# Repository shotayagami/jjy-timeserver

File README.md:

# JJY タイムサーバ (Raspberry Pi 4)

```
ntp.nict.jp ──NTP──▶ chrony ──システム時刻──▶ jjyd ──GPIO(ケーブル)──▶ JJY 送信ユニット ──40/60kHz(基板上のコイル)──▶ 電波時計
                       └──NTP──▶ 宅内LANのPC等
```

| ディレクトリ | 内容 |
|---|---|
| [hardware/](hardware/README.md) | 送信ユニット基板の回路・部品表・コイル・調整手順 |
| [hardware/kicad/](hardware/kicad) | KiCad 回路図・基板データ(100×96mm、J1 は上辺中央、基板上コイル、LCD、RTC) |
| [server/jjyd/](server/jjyd) | JJY エンコーダと送信デーモン(Python) |
| [server/config/](server/config) | chrony(NICT同期+LAN向けNTP) と jjyd の設定 |
| [server/systemd/](server/systemd) | systemd ユニット |
| [scripts/install.sh](scripts/install.sh) | Raspberry Pi OS 向けインストーラ |

## 仕組み

- **時刻取得**: chrony が `ntp.nict.jp` に 64 秒以上の間隔で問い合わせ、システム時刻を数 ms 以内に保つ。
- **フレーム生成**: [encoder.py](server/jjyd/encoder.py) が JST で 60 秒分のコード(分・時・通算日・年・曜日・パリティ)を作る。うるう秒は tzdata の leap-seconds.list から予定を読み、LS1/LS2 の予告(前月2日 9:00 JST 〜)と、実施月1日 8:59 JST の 61 秒(挿入)/59 秒(削除)フレームに対応する([leap.py](server/jjyd/leap.py)、`[leap]`)。挿入の 60 秒目は、カーネルが時計を1秒戻している間なので単調時計で送る。毎時 15 分・45 分も既定では通常フレームを送る。NICT 準拠の呼出符号フレーム(40〜49 秒に "JJY" のモールス、50〜55 秒を停波予告 ST に置き換え、年・曜日・うるう秒情報は送らない)は `[callsign] enabled = true` のときだけ送る(下の「法令・商標」参照)。
- **送信**: PWM0(GPIO18)が常時 40/60kHz を出し、GPIO23 が毎秒の頭で最大振幅にしてマーカー 0.2 s / "1" 0.5 s / "0" 0.8 s 後に 10% へ戻す。
- **表示**: 基板の LCD(16×2、I2C)に毎秒、日付・曜日・時刻・送信周波数・送信状態を表示する(`[lcd]`)。
- **送信信号 LED**: 低レベル期間だけ点灯する(ビット1=0.5秒、ビット0=0.2秒点灯して消灯、マーカー=0.8秒。`[signal]`)。
- **画面のモニタ**(`jjymon`): Pi の HDMI 画面に、JST の時計、jjyd が今送っているパルス(直近 10 秒の搬送波の波形)、1 分 60 秒のフレーム全体(今の秒を強調)、基板の LED D1(赤・高レベル)・D2(黄緑・低レベル)・D3(黄・通電)の点灯の再現、chrony の同期状態と時刻源の一覧、サービスの状態・CPU 温度を出す。jjyd が秒ごとに `/run/jjyd/status.json`(`[status]`)へ書く状態を読み、送信のタイミングには影響しない。インストーラが `/usr/local/bin/jjymon` と `/etc/xdg/autostart/jjymon.desktop`(デスクトップへのログイン時に全画面で自動起動。Esc で終了、F11 で全画面の切替)を入れる。不要なら `JJY_MONITOR=0` でインストールする。手で試すときは `jjymon --windowed`。LED は、フレームと時刻から jjyd の規則(`send_pulse`)どおりに計算した再現で、基板の GPIO を読んだものではない(基板が無くても動く)。
- **RTC が無い構成**(`JJY_RTC=0`): インストーラが `fake-hwclock` を入れ、時刻を 1 時間ごとと停止時に保存する(`systemd-timesyncd` を止めると、起動時の時計が古い保存時刻のままになるため)。起動直後のずれが縮まり、chrony が同期するまでの時計が実際に近くなる。jjyd は同期するまで送信しない。
- **RTC**: 基板上の DS3231 + CR2032 を使い、再起動直後でも前回同期から 24 時間以内なら送信を続ける(`[rtc]`、既定で有効)。
- **安全動作**: `chronyc tracking` が非同期なら送信停止。`local stratum 10` の自己参照(起動直後)や、同期先を選んだ後でもステップ補正が済むまで時計がずれている間(システム時刻のずれ 0.25 秒超)も、同期済みとみなさない(実機で起動直後に約 160 秒ずれていたため)。同期喪失後も `holdover_s`(既定6時間)までは送信継続。起動後に一度も同期していなければ送信しない。

## セットアップ

1. [hardware/README.md](hardware/README.md) に従い基板を製作し、Pi の GPIO ヘッダに**ケーブルでつなぐ**(40 ピンのフラットケーブル、またはジャンパ線)。基板は Pi のケースの外に置く。
2. Pi にこのリポジトリを置き `sudo ./scripts/install.sh` → `sudo reboot`
3. 確認
   - `chronyc sources -v` / `chronyc tracking` で NICT に同期していること
   - `sudo systemctl start jjyd && journalctl -u jjyd -f`
   - `python3 -m jjyd --dry-run` でハード無しでもタイミングログを確認可能
4. 既定は西日本 60kHz(はがね山)。東日本にする場合は `/etc/jjyd.toml` の `khz = 40` にして jjyd を再起動する(基板にスイッチは無く、周波数はソフトだけで切り替わる)。

## 開発・テスト

```
cd server
python -I tests/test_encoder.py        # エンコーダのラウンドトリップ/構造テスト
python -I tests/test_timesync.py       # 同期監視と RTC の判定
python -I tests/test_lcd_signal.py     # LCD 表示と信号 LED のタイミング
python -I tests/test_monitor.py        # モニタ(信号の再現、状態ファイル、chronyc の解析)
python -m jjyd --print-frame           # 現在の分のフレームを表示
# 画面の試験: 呼出符号のフレームを 20 分ごと(毎時 0・20・40 分)に出す。GPIO は使わず、状態は別のファイルへ書くので、動いている jjyd や jjymon には影響しない
python -m jjyd --dry-run --test-callsign-every 20 --status /tmp/jjy-test.json &
python -m jjymon --status /tmp/jjy-test.json --windowed
```

## 法令・商標

- **免許**: 免許が要らないのは、電波が[著しく微弱な無線局](https://laws.e-gov.go.jp/law/325M50080000014)(電波法第4条第1号、施行規則第6条: 322MHz以下では 3m で 500µV/m 以下)の範囲に収まる場合だけです。超えると無免許開設(電波法第110条)です。基板の出力は計算値で約 40µV/m(hardware/README.md)ですが、**実機での測定(告示の方法)は未実施**です。測定せずに出力を上げたり、外付けアンテナをつないだりしないでください。
- **呼出符号**: 「JJY」は NICT の局の呼出符号であり、NICT の登録商標(T4355749)でもあります。既定では送らず(`[callsign] enabled = false`)、15・45 分も通常のフレームを送ります。電波時計の受信にはこれで十分です。有効にするのは、用途と責任を理解したうえで自分で判断する場合だけにしてください。基板・ソフトを頒布・販売する場合は商標の扱いにも注意してください。
- **利用範囲**: 自分の時計を合わせる目的に限り、他人の機器に影響しない範囲(時計のすぐそば)で使ってください。ここに書いたことは法的助言ではありません。最終的な適法性の確認は利用者の責任です。

## 注意

- 電波は**微弱無線局の範囲(322MHz以下: 3mで500µV/m以下)**に収め、時計のすぐそばでのみ受かる出力にすること。
- 精度は Linux のユーザ空間タイミング(数百 µs〜数 ms)で、電波時計の許容(数十 ms)には十分。未確認の点は実機での電界強度と受信確認。
- 未実機検証: ハードウェア回路・sysfs PWM・systemd 部分は Pi 上でまだ試していない。エンコーダのみ PC でテスト済み。

## ライセンス

- ソフトウェア(`server/`、`scripts/`): [MIT License](LICENSE)
- ハードウェア(`hardware/` の回路図・基板・ガーバー・BOM): [CERN-OHL-P-2.0](hardware/LICENSE)(許容型)
- 基板データには KiCad 標準ライブラリのフットプリント/シンボルが含まれる。KiCad ライブラリのライセンス(CC-BY-SA 4.0 とデザインへの使用に関する例外)に従う。

## 現状と注意

- 設計段階のデータです。**基板は未発注・未製造で、Raspberry Pi 実機でも未検証**です(エンコーダとタイムシンクの単体テストと、KiCad の ERC/DRC のみ確認済み)。
- 電波は微弱無線局の範囲に収めること。各国・地域の電波法に従う責任は利用者にあります。
- 部品の在庫・品番は変動します。発注前に必ず再確認してください([hardware/kicad/fab/README.md](hardware/kicad/fab/README.md))。

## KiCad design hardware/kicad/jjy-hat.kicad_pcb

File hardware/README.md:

# JJY 送信ユニット(Raspberry Pi 4 用・40kHz / 60kHz ソフト切替)

Raspberry Pi の GPIO に**ケーブルでつなぐ**別基板です(Rev C)。次をすべて 1 枚に載せています。

- JJY 仕様の振幅変調(最大 100% / 低レベル 10%)をした 60kHz(はがね山・既定)/ 40kHz(おおたかどや山)の送信回路
- **アンテナ**: 基板上のスパイラルコイル(部品なし)と、外付けアンテナ用の端子(J2)の **2 択**(ジャンパ JP1 で選ぶ)
- 現在時刻を表示する LCD(16×2、I2C)と、送信信号を示す LED
- RTC(DS3231 + CR2032)

金属ケース(GPIO が細いスリットから見えるタイプ)の中の Pi にも使えるよう、Pi に挿す HAT ではなく、**ケースの外に置く基板**にしてあります(100×96mm)。
**J1 は基板の上辺の中央**にあり、ケーブルは上へ出ます。その下に送信回路と RTC、右下にコイル、左下に LCD の取り付け位置(J3)があります。

## Pi との接続(J1)

J1 は **2×20 の 2.54mm ピンヘッダ**(Pi の GPIO ヘッダと同じ並び・同じピン番号)です。2 通りの接続ができます。

- **40 ピンのフラットケーブル(1 対 1)**: Pi 側にメスのソケット、基板側に 2×20 の IDC ソケット。ピン 1 の印(赤線)を合わせる。
- **ジャンパ線(Dupont)**: 必要なピンだけを 1 本ずつつなぐ。

使うピン(Pi の物理ピン番号):

| 用途 | Pi のピン | 信号 |
|---|---|---|
| 電源 | 1 または 17 | 3V3 |
| GND | 6 / 9 / 14 など(どれか 1 本以上) | GND |
| I2C(LCD・RTC) | 3 / 5 | SDA(GPIO2)/ SCL(GPIO3) |
| キャリア | 12 | GPIO18(PWM0) |
| 振幅切替 | 16 | GPIO23 |
| 送信信号 LED | 18 | GPIO24 |

- **ケースへの配線**: ケースの蓋にピンの名前が印刷されているので、見ながらつなげる。スリットの寸法・深さは**実物で確認**すること(ソケットが入らない場合は、ジャンパ線を使う)。
- 基板側の J1 は、使う信号だけジャンパ線でつなげば、40 ピンすべてを配線する必要はない。

## 回路

```
 GPIO18 ──┬──────── U1A in (2), U1B in (5)  (R4 10k で GND へプルダウン)
 GPIO23 ──┴─── U1B /OE (4) ─── R3 10k で 3V3 へプルアップ、D1 のカソードへ
                                   3V3 ── R5 1k ── D1(赤 LED)
 U1A(/OE=GND, 常時有効)出力 ── R1 10k ──┐
                                           ├── 駆動ノード ── JP1 ─┬─(2-3)─ L1(基板コイル)── GND
                                           │                      └─(1-2)─ J2(外付けアンテナ)── GND
 U1B(GPIO23=Low で有効)出力 ── R2 1.1k ──┘

 GPIO24 ── R7 330 ── D2(緑 LED)── GND      送信信号 LED
 3V3 ── R8 470 ── D3(黄 LED)── GND          通電表示(パイロットランプ。常時点灯)
 U1: VCC(14)=3V3 (C1 100nF)、GND(7)。未使用ゲート(C, D)の入力は GND。
```

- **U1A** は常にキャリアを出す(R1 経由 = 低レベル)。**U1B** は GPIO23 が Low の間だけ加わる(R2 が並列 = 高レベル)。
- 高レベルと低レベルの電流比は、駆動抵抗がコイルより十分大きいので **1 + R1/R2**(= 約 10.1 倍、-20dB、約 10%)。
- D1(赤)は高レベル(最大振幅)の間だけ点灯する(0.2 / 0.5 / 0.8 秒)。

## 部品表

| 記号 | 部品 | 備考 |
|---|---|---|
| U1 | 74LVC125A(SOIC-14、LCSC C7661) | JLCPCB で実装 |
| U2 | DS3231SN#(SOIC-16W、LCSC C722469) | JLCPCB で実装(RTC) |
| K1 | AQY212SX(フォトモスリレー、SOP-4、LCSC C719754) | JLCPCB で実装(共振オプション用。通常は使わない) |
| J1 | 2×20 ピンヘッダ(2.54mm、ストレート) | 手はんだ |
| R1 | 10kΩ 1/4W 金属皮膜 1%(リード) | 常時キャリア。R2 の約 9 倍にする |
| R2 | 1.1kΩ 1/4W 金属皮膜 1%(リード) | 高レベルのとき並列 |
| R3, R4 | 10kΩ 1/4W(リード) | プルアップ/プルダウン |
| R5 | 1kΩ 1/4W(リード) | D1 の電流制限 |
| R7 | 330Ω 1/4W(リード) | D2 の電流制限 |
| R8 | 470Ω 1/4W(リード) | D3 の電流制限(約 2.8mA) |
| D1 | 3mm 赤 LED(リード、Vf 約 2V) | 高レベル表示。四角いパッドがカソード |
| D2 | 3mm 緑 LED(リード、Vf 約 2V) | 送信信号 LED。四角いパッドがカソード |
| D3 | 3mm 黄 LED(リード、Vf 約 2V) | 通電表示(パイロットランプ)。四角いパッドがカソード |
| C1, C6 | 100nF 50V 積層セラミック(リード、足の間隔 5.08mm) | U1 / U2 のバイパス |
| BT1 | CR2032 ホルダ MYOUNG BS-07-A1BJ001(LCSC C2979167) + CR2032 | RTC のバックアップ。手はんだ |
| J3 | 1×4 ピンソケット(2.54mm) | LCD 用(下記) |
| L1 | 基板上のスパイラルコイル | 部品は不要(基板の配線) |
| JP1 | 1×3 ピンヘッダ(2.54mm)+ 短絡ピン(ジャンパ)1 個 | アンテナ選択。1-2 短絡 = 外付け(J2)/ 2-3 短絡 = 基板コイル |
| J2 | 1×2 ピンヘッダ(2.54mm) | 外付けアンテナ(コイル)の接続。向きは問わない |

リード部品は**手はんだ**です(JLCPCB では実装しません)。抵抗は縦置き(足の間隔 2.54mm)、コンデンサは基板の穴が 5.00mm なので足を少し曲げて入れます。

## アンテナの選択(JP1)と外付けアンテナ(J2)

駆動信号は JP1 の中央のピン(2)に来ています。**短絡ピン(ジャンパ)をどちらに挿すかで、アンテナを選びます**(選ばれなかった側は開放になり、電波は出ません)。

| JP1 の短絡 | 使うアンテナ |
|---|---|
| 1-2 | 外付けアンテナ(J2 に接続) |
| 2-3 | 基板コイル(L1)← 標準 |
| なし | どちらにも出力しない |

### 外付けアンテナを使うとき(重要: R1/R2 を交換する)
- 外付けのフェライトバーなどは、基板のコイルよりずっと強い磁界が出ます(巻数 × 断面積 × 棒の透磁率が大きいため)。**基板コイル用の R1/R2(10kΩ / 1.1kΩ、電流 約 2mA)のままつなぐと、微弱無線局の限度を超えるおそれがあります。**
- そこで、外付けアンテナに替えるときは、**R1 と R2 をもっと大きな値に交換**して電流を減らします(リード部品なので交換は容易)。比は R1 = 約 9 × R2 を保ちます。
- 目安(フェライトバー: 直径 10mm × 長さ 100mm、100 回巻きの場合。**概算なので必ず実測で確認**):

| R1 / R2 | 電流(基本波のピーク) | 備考 |
|---|---|---|
| 220kΩ / 24kΩ | 約 0.1mA | 最初はこの値から。受からなければ下げる |
| 100kΩ / 11kΩ | 約 0.2mA | |
| 68kΩ / 7.5kΩ | 約 0.3mA | 概算で限度に近づく。実測が必須 |

- 巻数が少ない小さなコイルなら、基板コイル用の値(10kΩ / 1.1kΩ)のままでも使えます。目安は「巻数 × 面積 × 電流」が基板コイル(30 回 × 約 3cm² × 2mA)と同程度までです。
- 基板コイルに戻すときは、R1/R2 を 10kΩ / 1.1kΩ に戻し、JP1 を 2-3 にします。
- J2 のコイルには直流が流れません(駆動は交流のみ)。インダクタンスは 0.1〜3mH 程度で、厳密でなくて構いません(共振させていないため)。

## 共振オプション(外付けアンテナ用・通常は未実装)

外付けアンテナ(J2)側には、以前の設計と同じ**直列共振回路と、40kHz / 60kHz をソフトで切り替えるフォトモスリレー K1**の部品を置く場所を用意してあります(K1 だけは JLCPCB で実装済み、他の部品は**載せない**のが標準)。基板コイル(L1)側には影響しません。

構成(JP1 を 1-2 にしたとき): `JP1.1 → [共振コンデンサ] → J2.1(外付けアンテナ)→ GND`

| 記号 | 部品 | 役割 |
|---|---|---|
| JP2 | 1×2 ピンヘッダ + 短絡ピン | 短絡 = 共振回路をバイパス(標準)/ 短絡なし = 共振コンデンサを通す |
| C2・C3・C4 | 4.7nF・2.2nF・150pF(C0G、50V、±5%) | 60kHz 用(合計 7.05nF、1mH のコイルで約 59.9kHz) |
| C5 | 数 pF〜数十 pF | 60kHz の微調整用 |
| C7・C8・C9 | 4.7nF・2.2nF・2.2nF(C0G、50V、±5%) | 40kHz 用に K1 経由で追加(合計 16.15nF で約 39.6kHz) |
| K1 | AQY212SX(フォトモスリレー、SOP-4、LCSC C719754) | 実装済み。GPIO21(J1 の 40 番ピン)で 40kHz 用の C7〜C9 を接続 |
| R6 | 330Ω 1/4W | K1 の LED の電流制限 |

### 実装する手順
1. JP2 の短絡ピンを外す。
2. C2・C3・C4(と必要なら C5)を実装する。1mH 前後の外付けコイルなら、60kHz で共振する。
3. 40kHz も使うなら、R6・C7〜C9 も手はんだする(K1 は実装済み)。
4. `/etc/jjyd.toml` の `select_gpio = 21` の行を有効にして、`sudo systemctl restart jjyd`。40kHz のときだけ GPIO21 が High になり、K1 が C7〜C9 を追加する。
5. 同調は使うコイルの L で変わるので、**各周波数でアンテナ電流を測って調整**する(C = 1 / ((2πf)² · L))。

### 注意(重要)
- 共振させると電流が増えます。共振の効果は、駆動抵抗(R1/R2 の並列)がコイルのリアクタンス(1mH・60kHz で約 380Ω)と同程度以下のときに出ます。標準の R1/R2(10kΩ / 1.1kΩ)では、共振させても電流はほとんど変わりません。
- 共振で電流を増やすために R1/R2 を小さくすると、**微弱無線局の限度を超えやすくなります**。外付けコイルの巻数を減らす、電流を測る、など実測で確認してください。
- K1 は SMD 部品で、JLCPCB が実装します(R6 と C7〜C9 が無いうちは何も接続されず、動作に影響しません)。ピン配置(1=LED+、2=LED−、3/4=負荷)と LED 電流はデータシートで未確認です。
- 未確認: この共振オプションは、実機で試していません。

## アンテナ(基板上のスパイラルコイル L1)

基板の右下に、外形 26mm 角の**四角いスパイラルコイル**を両面に作っています(表面は外側から内側へ、中心の穴で裏面へ移り、裏面は内側から外側へ)。

| 項目 | 値(生成スクリプトの計算 / 概算) |
|---|---|
| 巻数 | 約 15 回/面、合計約 30 回 |
| 配線長 | 約 2m(幅 0.25mm、ピッチ 0.6mm) |
| 直流抵抗 | 約 4Ω |
| インダクタンス | 約 15µH(概算。実測すること) |

- **共振はさせません**。駆動抵抗(約 1kΩ)がコイルのリアクタンス(60kHz で約 6Ω)よりはるかに大きいので、電流は抵抗だけで決まります。そのため、従来の共振コンデンサと帯域切替のスイッチ(K1)は**廃止**しました。40kHz / 60kHz の切替は**ソフトの `khz` の設定だけ**です。
- **銅ベタ禁止**: コイルの範囲は、表裏とも GND の銅ベタを抜いてあります(コイルの下に銅があると、渦電流で磁界が弱くなります)。
- **金属を近づけない**: コイルの近く(特に上や下)に金属板を置かないでください。
- 高レベルのアンテナ電流は約 2mA(2.1V ÷ R1・R2 の並列 約 1kΩ)。コイルが小さい分、電流を大きくして磁界の強さを保っている。

### 電界強度の概算(重要・実測で必ず確認)
上のコイルを、巻数 30、平均面積 2.9×10⁻⁴ m²、電流 2mA の磁気双極子として概算した値です。**概算は数十 dB の誤差があり得ます。**

| 距離 | 電界強度の目安 | 備考 |
|---|---|---|
| 3m | 約 40µV/m | 微弱無線局の限度(3m で 500µV/m)に対して約 20dB の余裕 |
| 1m | 約 1mV/m | |
| 0.3m | 約 40mV/m | 時計に近づける距離 |

- 時計は、基板のコイルの上や横に、**数 cm〜30cm** まで近づけて使います。
- 受信できないときは、(1) 近づける、(2) R1/R2 を同じ倍率で下げて電流を増やす(比 R1 = 約 9 × R2 を保つ)、の順に試します。
- **出力を上げた場合は、微弱無線局の範囲を超えていないか、必ず測定で確認してください。**

### R1 と R2 を変えるときのルール
- 高低の比(約 10:1 = -20dB)を保つには **R1 = 約 9 × R2**(電流比は 1 + R1/R2)。
- 出力を変えるときは、R1 と R2 を**同じ倍率**で変えます。電流は並列抵抗(≒ R1/10)にほぼ反比例します。
- 例: 10k/1.1k(既定、約 2mA)、22k/2.4k(約 1mA)、68k/7.5k(約 0.3mA)。
- R2 は 330Ω 以上にします(74LVC125 の出力抵抗が約 25Ω あり、小さいと比が崩れます)。

## 時刻表示 LCD(J3)と送信信号 LED(D2)

### LCD(J3)
- 16×2 文字 LCD(I2C、3.3V、ST7032 系)。秋月電子の次の 2 点を想定(**LCD 本体と変換基板は別売り**)。
  - LCD 本体: AQM1602XA-RN-GBW(秋月通販コード 108779、680 円)。
  - ピッチ変換キット: AE-AQM1602A(KIT)(秋月通販コード 108896、780 円)。LCD 本体の細かいピッチの端子(9 本)を、変換基板にはんだ付けする。
  - 秋月の在庫は 2026-10-30 時点で「在庫あり」(確認済み。在庫は変動する)。
- J3 は 1×4 の**メスのピンソケット**で、基板の左下にある。変換基板の並び(**1 +V / 2 SCL / 3 SDA / 4 GND**)に合わせてある(基板上では上から GND / SDA / SCL / +V の順に並ぶ。向きを逆にして、I2C の配線が交差しないようにしている)。変換基板の 1×4 ピンヘッダ(キット付属かを確認)をはんだ付けして、J3 に挿す。ケーブルで離して置いてもよい。
- I2C のプルアップは Pi 側(1.8kΩ)を使うので、変換基板の**プルアップ用ジャンパはオープンのまま**にする。
- I2C アドレスは 0x3E(RTC の 0x68 と衝突しない)。
- 未確認: LCD 本体を J3 に挿したときの向き・張り出し(モジュールの寸法は 66×27.7mm)。J3 は基板の左下にあり、LCD は J3 から右へ約 66mm、下側の帯に載る想定(右端はコイルの近くまで来るので、LCD の金属部分がコイルに近づかないか実物で確認すること)。
- ソフト: `/etc/jjyd.toml` の `[lcd]`(`enabled`、`bus`、`address`、`contrast`)。1 行目に日付と曜日、2 行目に時刻・送信周波数・状態(`TX` = 送信中、`OFF` = 停止)を毎秒表示する。表示が薄い/濃いときは `contrast`(0〜63)を調整。LCD が無くても送信は続く。

### 送信信号 LED(D2)
- GPIO24 → R7(330Ω)→ D2(3mm 緑 LED)→ GND。
- 点灯のルール(低レベル期間だけ点灯): ビット 1 = 0.5 秒点灯 / ビット 0 = 0.2 秒点灯して消灯 / マーカー = 0.8 秒点灯。高レベルの間は消灯し、高レベルが終わると点灯、次の秒頭で消灯する。
- D1(赤、高レベルの間だけ点灯)と見比べると、パルスの形が分かる。
- ソフト: `/etc/jjyd.toml` の `[signal] gpio = 24`。

## RTC(基板上に実装)

DS3231SN(U2)と CR2032 ホルダ(BT1)を載せてあり、再起動直後でも NTP 同期を待たずに送信を再開できます。

- 配線: SDA = GPIO2、SCL = GPIO3、VCC = 3V3、VBAT = BT1 の +。I2C のプルアップは Pi 側(1.8kΩ)を使う。
- U2 は 32kHz / INT / RST を未接続にしている。C6 100nF が U2 のバイパス。
- BT1 は **手はんだ**。**極性(パッド 1 = +)を確認すること**(KiCad 標準フットプリントのシルクにも「+」がパッド 1 側に描かれているが、ホルダのデータシートでも確認する)。電池は 1 次電池(CR2032)。
- ソフト: `sudo ./scripts/install.sh` が `dtoverlay=i2c-rtc,ds3231` を有効化し、`/etc/jjyd.toml` の `[rtc] enabled = true` にする(既定)。前回同期から 24 時間以内なら、再起動直後に NTP 未同期でも送信を許可する。
- 未確認: Raspberry Pi 実機での RTC 動作(オーバーレイ・udev の手順は一般的な手順に沿ったもので、実機では未検証)。

## 調整手順

1. `sudo systemctl stop jjyd` のあと、実機で `sudo python3 -m jjyd` を起動する。
2. オシロで GPIO18 が 60kHz であること、GPIO23 が 1 秒周期で Low パルスになること(0.2 / 0.5 / 0.8 秒)を確認する。
3. 駆動ノード(R1/R2 とコイルの接続点)で、1 秒ごとに振幅が約 10:1 に変わることを確認する。
4. 電波時計をコイルの近くに置き、強制受信(多くは手動の受信ボタン)を試す。受信には約 2〜3 分(連続 2 フレームの確認)必要。
5. 受信できないときは、時計との距離・向き、`khz`(60 / 40)が時計の対応する局と合っているか、金属の近さを確認する。

## KiCad データ

[kicad/](kicad) に KiCad 8 以降で開けるプロジェクト(`jjy-hat.kicad_pro`)があります(ファイル名は旧称のまま)。
基板は 100×96mm、2 層。J1 は上辺の中央、部品は表面(SMD は U1・U2・K1 のみ、他はリード部品)で、取り付け穴は四隅です。
プレビュー: [jjy-hat-pcb-preview.png](kicad/jjy-hat-pcb-preview.png)

- データは [kicad/gen_kicad.py](kicad/gen_kicad.py) で生成しています。部品値や配置、コイルの寸法(`COIL_*`)を変えるときは、このスクリプトを直して `python -I gen_kicad.py` で再生成します。
- フットプリント・シンボルは KiCad 標準ライブラリの実物を使い、自作の部品(74LVC125・DS3231SN・AQY212S の記号と、スパイラルコイルのフットプリント)はプロジェクト内のライブラリ([JJY.kicad_sym](kicad/JJY.kicad_sym)、[JJY.pretty/](kicad/JJY.pretty))にまとめています。
- コイルは銅箔の図形でできたフットプリントで、ネットタイ(DRV と GND のパッドを同じ導体でつなぐ宣言)にしています。
- KiCad 10.0.7 の ERC/DRC を実行して、**ERC 0 件・DRC 0 件(警告を含む)・未配線 0・回路図と基板の不一致 0**を確認済みです。
- 初回に開いたら、基板エディタで `B` キー(ゾーン再充填)を押して GND ベタを塗り直してください(コイルの範囲は銅ベタが入らない設定です)。
- 未確認: 実際の製造(基板メーカーのチェック)、コイルの実測(インダクタンス・電界強度)、実機動作。

## 履歴

- Rev A: 60kHz、Pi に挿す HAT 形、チップ部品、1mH のフェライトバー用の共振回路。
- Rev B: 40/60kHz 切替(フォトモスリレーで共振コンデンサを切替)、RTC、LCD、送信信号 LED。
- Rev C(現在): ケースの外に置く基板に変更(Pi とは GPIO のケーブルでつなぐ)、アンテナを基板上のスパイラルコイルに変更。共振回路と帯域切替(K1・C2〜C9)は廃止し、帯域はソフトのみで切替。外付けアンテナ用の J2 と、基板コイルとの選択ジャンパ JP1 を追加。外付け側の共振オプション(C2〜C9・R6・JP2)は未実装(DNP)で場所だけ用意し、K1 は JLCPCB で実装。

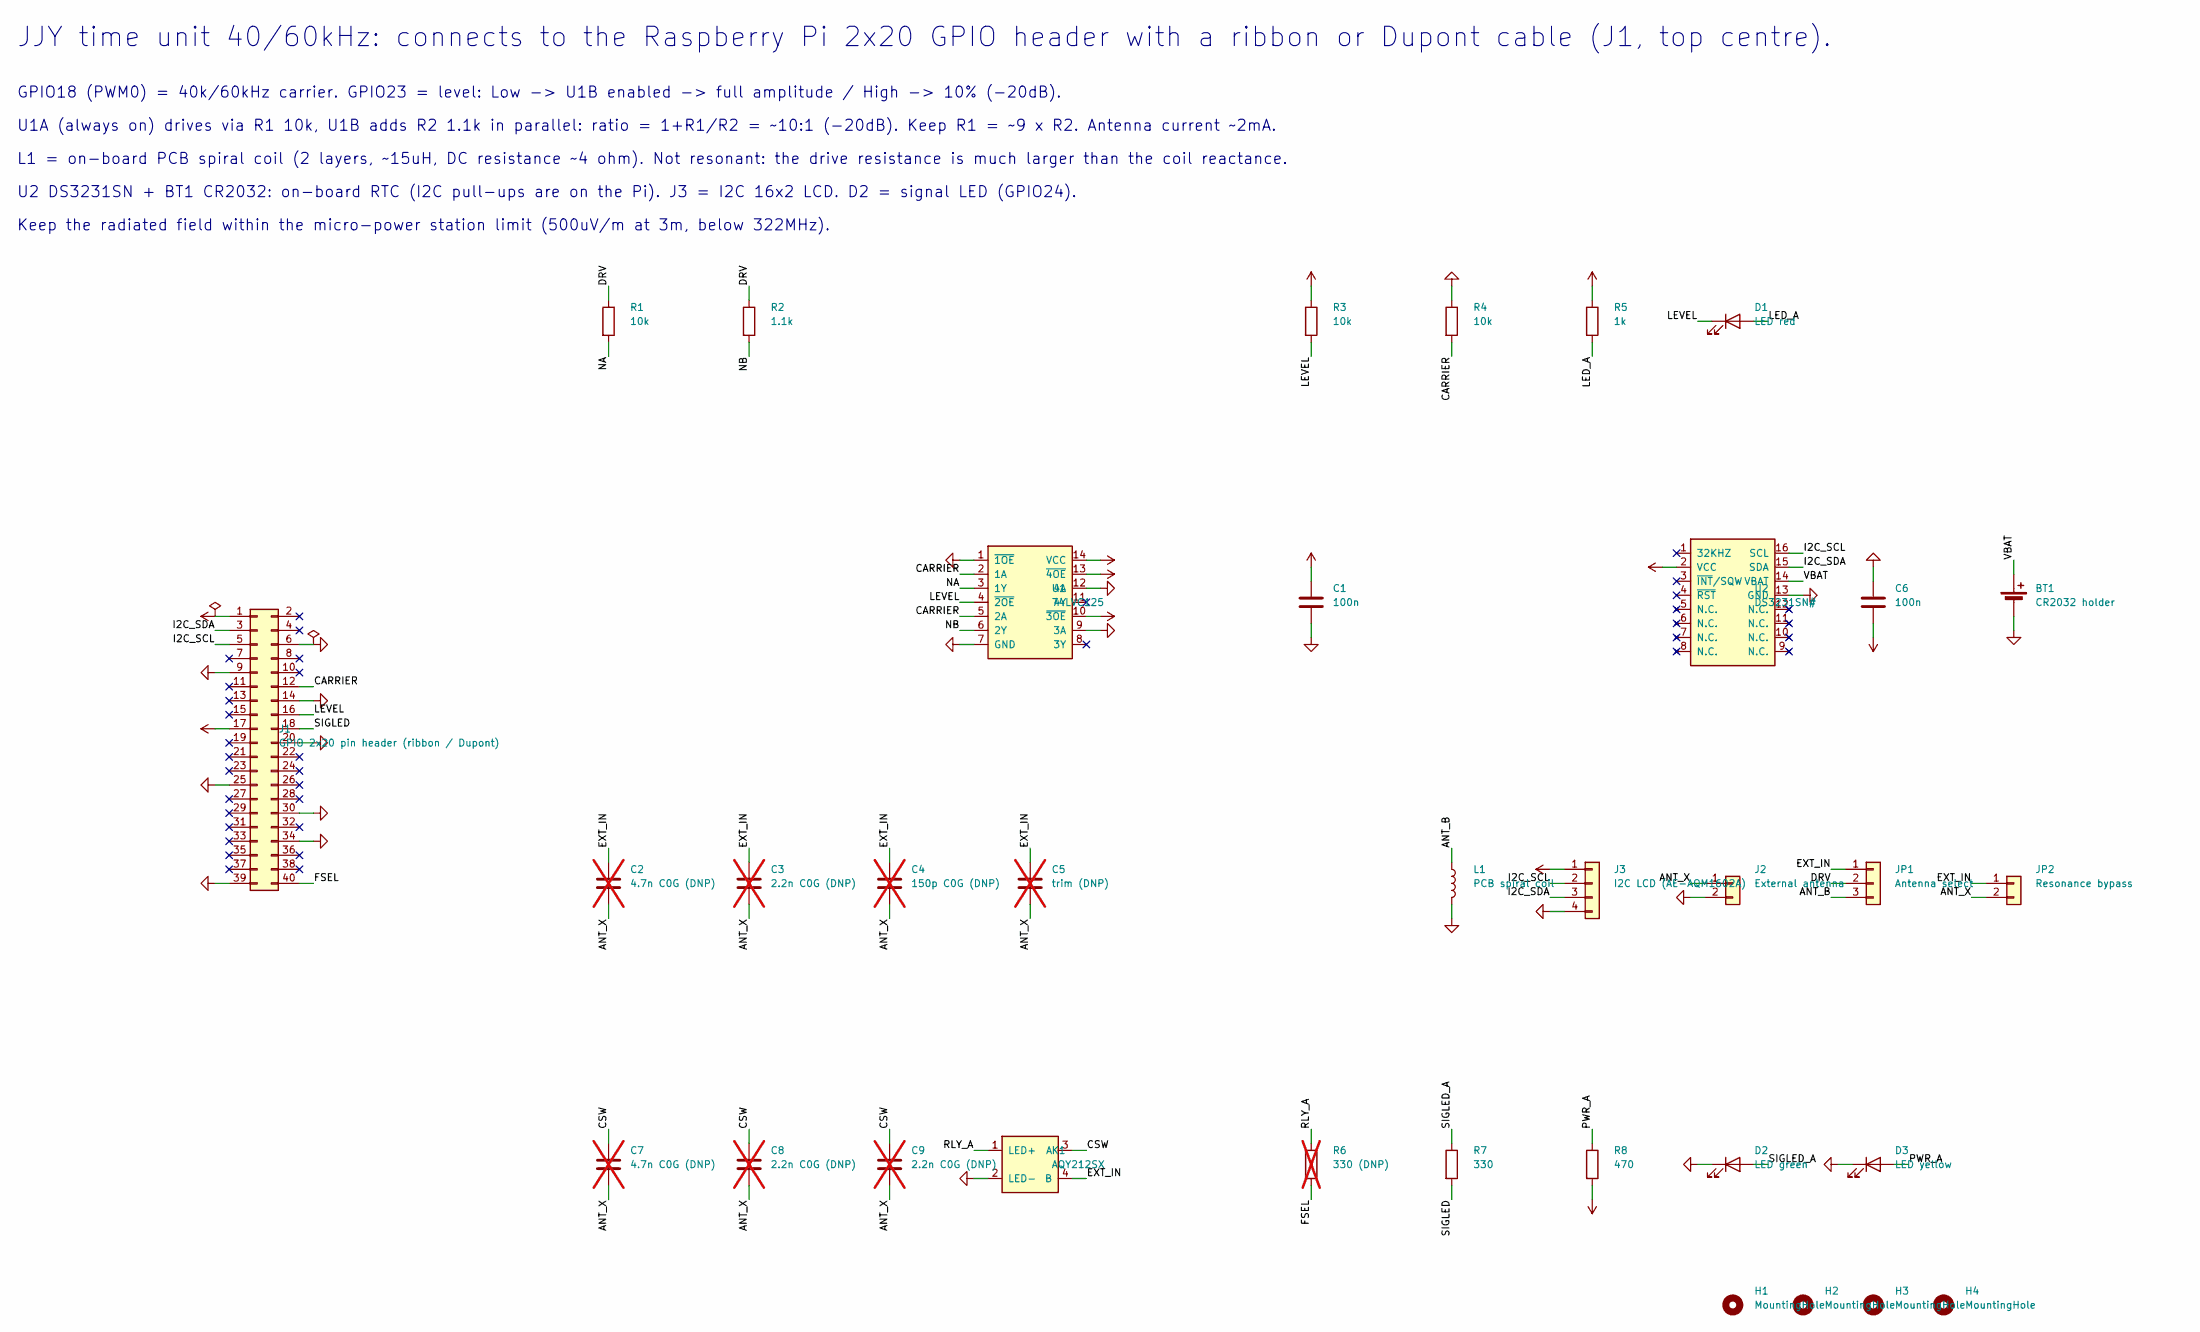
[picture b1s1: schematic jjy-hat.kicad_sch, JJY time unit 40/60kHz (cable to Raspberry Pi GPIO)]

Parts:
BT1: CR2032 holder; BatteryHolder_MYOUNG_BS-07-A1BJ001_CR2032
C1, C6: 100n; C_Rect_L7.0mm_W2.0mm_P5.00mm
C2, C7: 4.7n C0G (DNP); C_Rect_L7.0mm_W2.0mm_P5.00mm; not fitted
C3, C8, C9: 2.2n C0G (DNP); C_Rect_L7.0mm_W2.0mm_P5.00mm; not fitted
C4: 150p C0G (DNP); C_Rect_L7.0mm_W2.0mm_P5.00mm; not fitted
C5: trim (DNP); C_Rect_L7.0mm_W2.0mm_P5.00mm; not fitted
D1: LED red; LED_D3.0mm
D2: LED green; LED_D3.0mm
D3: LED yellow; LED_D3.0mm
H1, H2, H3, H4: MountingHole; MountingHole_2.7mm_M2.5
J1: GPIO 2x20 pin header (ribbon / Dupont); PinHeader_2x20_P2.54mm_Vertical
J2: External antenna; PinHeader_1x02_P2.54mm_Vertical
J3: I2C LCD (AE-AQM1602A); PinSocket_1x04_P2.54mm_Vertical
JP1: Antenna select; PinHeader_1x03_P2.54mm_Vertical
JP2: Resonance bypass; PinHeader_1x02_P2.54mm_Vertical
K1: AQY212SX; SO-4_4.4x4.3mm_P2.54mm
L1: PCB spiral coil; Coil_Spiral
R1, R3, R4: 10k; R_Axial_DIN0207_L6.3mm_D2.5mm_P2.54mm_Vertical
R2: 1.1k; R_Axial_DIN0207_L6.3mm_D2.5mm_P2.54mm_Vertical
R5: 1k; R_Axial_DIN0207_L6.3mm_D2.5mm_P2.54mm_Vertical
R6: 330 (DNP); R_Axial_DIN0207_L6.3mm_D2.5mm_P2.54mm_Vertical; not fitted
R7: 330; R_Axial_DIN0207_L6.3mm_D2.5mm_P2.54mm_Vertical
R8: 470; R_Axial_DIN0207_L6.3mm_D2.5mm_P2.54mm_Vertical
U1: 74LVC125; SOIC-14_3.9x8.7mm_P1.27mm
U2: DS3231SN#; SOIC-16W_7.5x10.3mm_P1.27mm

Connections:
+3V3: C1.1, C6.2, J1.1, J1.17, J3.1, R3.1, R5.1, R8.2, U1.10 (~3OE), U1.13 (~4OE), U1.14 (VCC), U2.2 (VCC)
/ANT_B: JP1.3, L1.1
/ANT_X: C2.2, C3.2, C4.2, C5.2, C7.2, C8.2, C9.2, J2.1, JP2.2
/CARRIER: J1.12, R4.2, U1.2 (1A), U1.5 (2A)
/CSW: C7.1, C8.1, C9.1, K1.3 (A)
/DRV: JP1.2, R1.1, R2.1
/EXT_IN: C2.1, C3.1, C4.1, C5.1, JP1.1, JP2.1, K1.4 (B)
/FSEL: J1.40, R6.2
/I2C_SCL: J1.5, J3.2, U2.16 (SCL)
/I2C_SDA: J1.3, J3.3, U2.15 (SDA)
/LED_A: D1.2 (A), R5.2
/LEVEL: D1.1 (K), J1.16, R3.2, U1.4 (~2OE)
/NA: R1.2, U1.3 (1Y)
/NB: R2.2, U1.6 (2Y)
/PWR_A: D3.2 (A), R8.1
/RLY_A: K1.1 (LED+), R6.1
/SIGLED: J1.18, R7.2
/SIGLED_A: D2.2 (A), R7.1
/VBAT: BT1.1 (+), U2.14 (VBAT)
GND: BT1.2 (-), C1.2, C6.1, D2.1 (K), D3.1 (K), J1.6, J1.9, J1.14, J1.20, J1.25, J1.30, J1.34, J1.39, J2.2, J3.4, K1.2 (LED-), L1.2, R4.1, U1.1 (~1OE), U1.7 (GND), U1.9 (3A), U1.12 (4A), U2.13 (GND)

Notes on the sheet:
JJY time unit 40/60kHz: connects to the Raspberry Pi 2x20 GPIO header with a ribbon or Dupont cable (J1, top centre).
GPIO18 (PWM0) = 40k/60kHz carrier. GPIO23 = level: Low -> U1B enabled -> full amplitude / High -> 10% (-20dB).
U1A (always on) drives via R1 10k, U1B adds R2 1.1k in parallel: ratio = 1+R1/R2 = ~10:1 (-20dB). Keep R1 = ~9 x R2. Antenna current ~2mA.
L1 = on-board PCB spiral coil (2 layers, ~15uH, DC resistance ~4 ohm). Not resonant: the drive resistance is much larger than the coil reactance.
U2 DS3231SN + BT1 CR2032: on-board RTC (I2C pull-ups are on the Pi). J3 = I2C 16x2 LCD. D2 = signal LED (GPIO24).
Keep the radiated field within the micro-power station limit (500uV/m at 3m, below 322MHz).

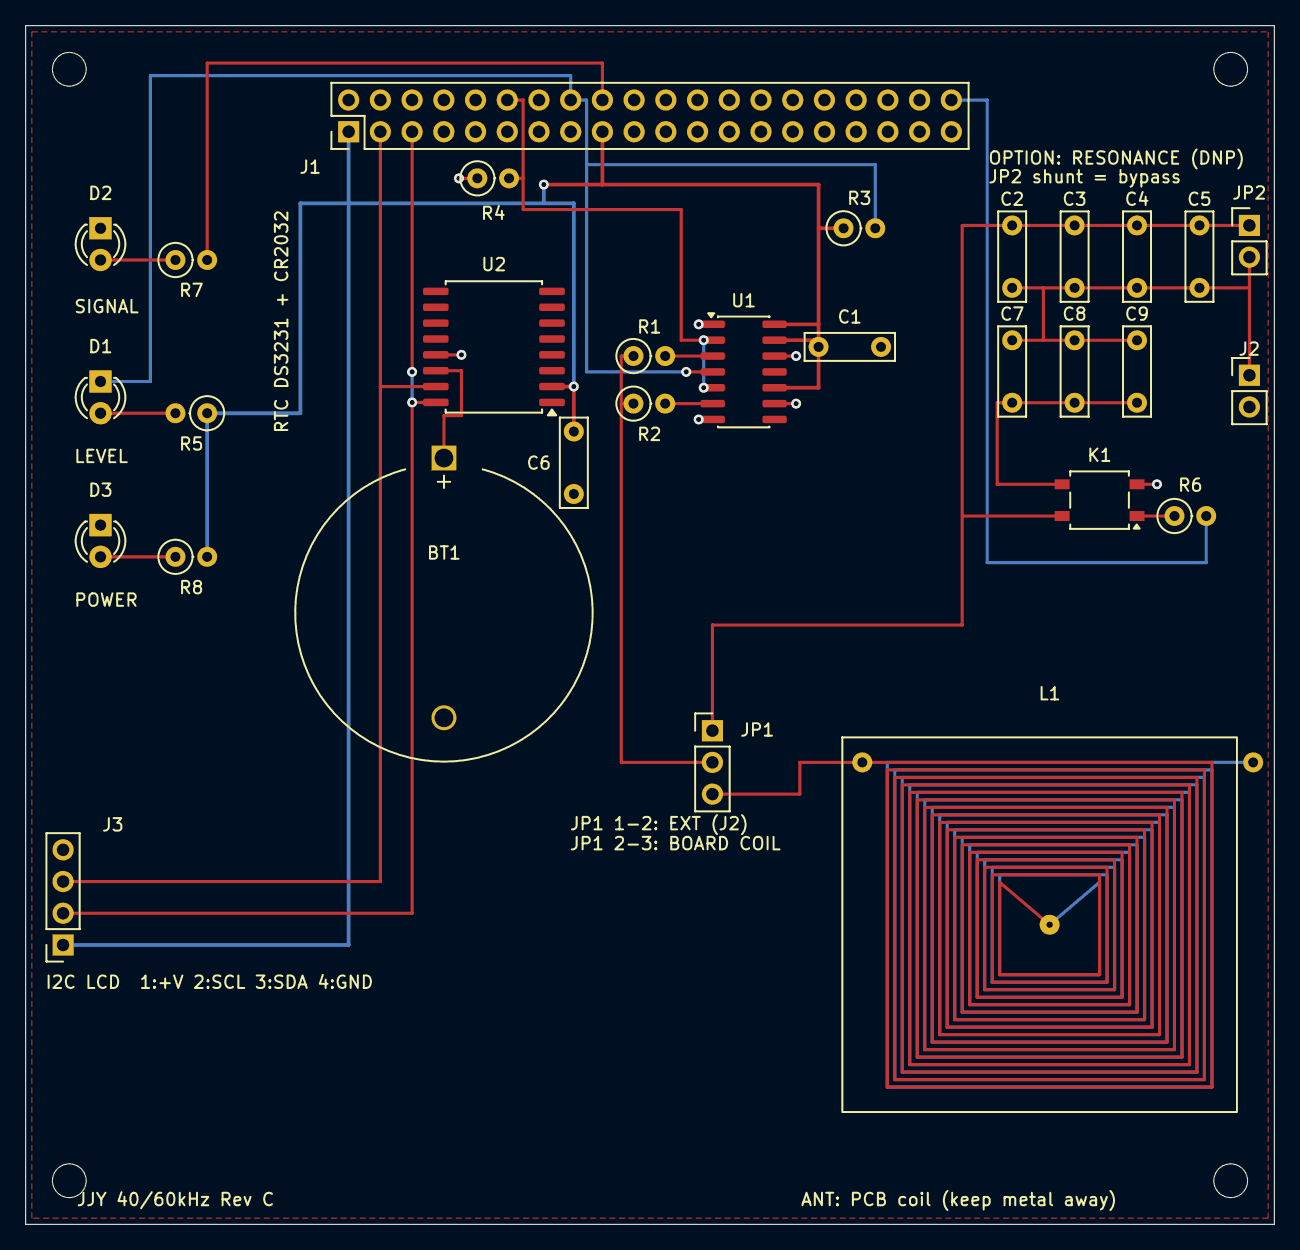
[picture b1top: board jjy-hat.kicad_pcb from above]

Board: 2 copper layers, 100.0 x 96.0 mm, 34 parts (0 on the bottom side), 20 nets.

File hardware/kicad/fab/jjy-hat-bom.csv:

"Designator","Value","Footprint","Qty","DNP"
"BT1","CR2032 holder","Battery:BatteryHolder_MYOUNG_BS-07-A1BJ001_CR2032","1",""
"C1,C6","100n","Capacitor_THT:C_Rect_L7.0mm_W2.0mm_P5.00mm","2",""
"C2,C7","4.7n C0G (DNP)","Capacitor_THT:C_Rect_L7.0mm_W2.0mm_P5.00mm","2","未実装(DNP)"
"C3,C8,C9","2.2n C0G (DNP)","Capacitor_THT:C_Rect_L7.0mm_W2.0mm_P5.00mm","3","未実装(DNP)"
"C4","150p C0G (DNP)","Capacitor_THT:C_Rect_L7.0mm_W2.0mm_P5.00mm","1","未実装(DNP)"
"C5","trim (DNP)","Capacitor_THT:C_Rect_L7.0mm_W2.0mm_P5.00mm","1","未実装(DNP)"
"D1","LED red","LED_THT:LED_D3.0mm","1",""
"D2","LED green","LED_THT:LED_D3.0mm","1",""
"D3","LED yellow","LED_THT:LED_D3.0mm","1",""
"J1","GPIO 2x20 pin header (ribbon / Dupont)","Connector_PinHeader_2.54mm:PinHeader_2x20_P2.54mm_Vertical","1",""
"J2","External antenna","Connector_PinHeader_2.54mm:PinHeader_1x02_P2.54mm_Vertical","1",""
"J3","I2C LCD (AE-AQM1602A)","Connector_PinSocket_2.54mm:PinSocket_1x04_P2.54mm_Vertical","1",""
"JP1","Antenna select","Connector_PinHeader_2.54mm:PinHeader_1x03_P2.54mm_Vertical","1",""
"JP2","Resonance bypass","Connector_PinHeader_2.54mm:PinHeader_1x02_P2.54mm_Vertical","1",""
"K1","AQY212SX","Package_SO:SO-4_4.4x4.3mm_P2.54mm","1",""
"L1","PCB spiral coil","JJY:Coil_Spiral","1",""
"R1,R3,R4","10k","Resistor_THT:R_Axial_DIN0207_L6.3mm_D2.5mm_P2.54mm_Vertical","3",""
"R2","1.1k","Resistor_THT:R_Axial_DIN0207_L6.3mm_D2.5mm_P2.54mm_Vertical","1",""
"R5","1k","Resistor_THT:R_Axial_DIN0207_L6.3mm_D2.5mm_P2.54mm_Vertical","1",""
"R6","330 (DNP)","Resistor_THT:R_Axial_DIN0207_L6.3mm_D2.5mm_P2.54mm_Vertical","1","未実装(DNP)"
"R7","330","Resistor_THT:R_Axial_DIN0207_L6.3mm_D2.5mm_P2.54mm_Vertical","1",""
"R8","470","Resistor_THT:R_Axial_DIN0207_L6.3mm_D2.5mm_P2.54mm_Vertical","1",""
"U1","74LVC125","Package_SO:SOIC-14_3.9x8.7mm_P1.27mm","1",""
"U2","DS3231SN#","Package_SO:SOIC-16W_7.5x10.3mm_P1.27mm","1",""
